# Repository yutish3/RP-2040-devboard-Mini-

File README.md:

### ABOUT 
rp-2040 dev board in small form factor of 3cm x 6cm made in kicad

it has :- 2 x 20 pin connectors , separate headers for HC - 05 Bluetooth module , extra 4Mb flash memory , USB c port , 2 buttons for BOOT and Reset and TC2030 connector for programming without usb c

# IMAGES

# SCHEMATICS 

# FOOTPRINTS

# PCB

# RENDER

Initially i tried to make it black but it changed color to smth random and it looks way cooler now 

# FILES
/Production folder has all the production files

/PCB files has all the pcb project files in it

# CREDITS

Kicad

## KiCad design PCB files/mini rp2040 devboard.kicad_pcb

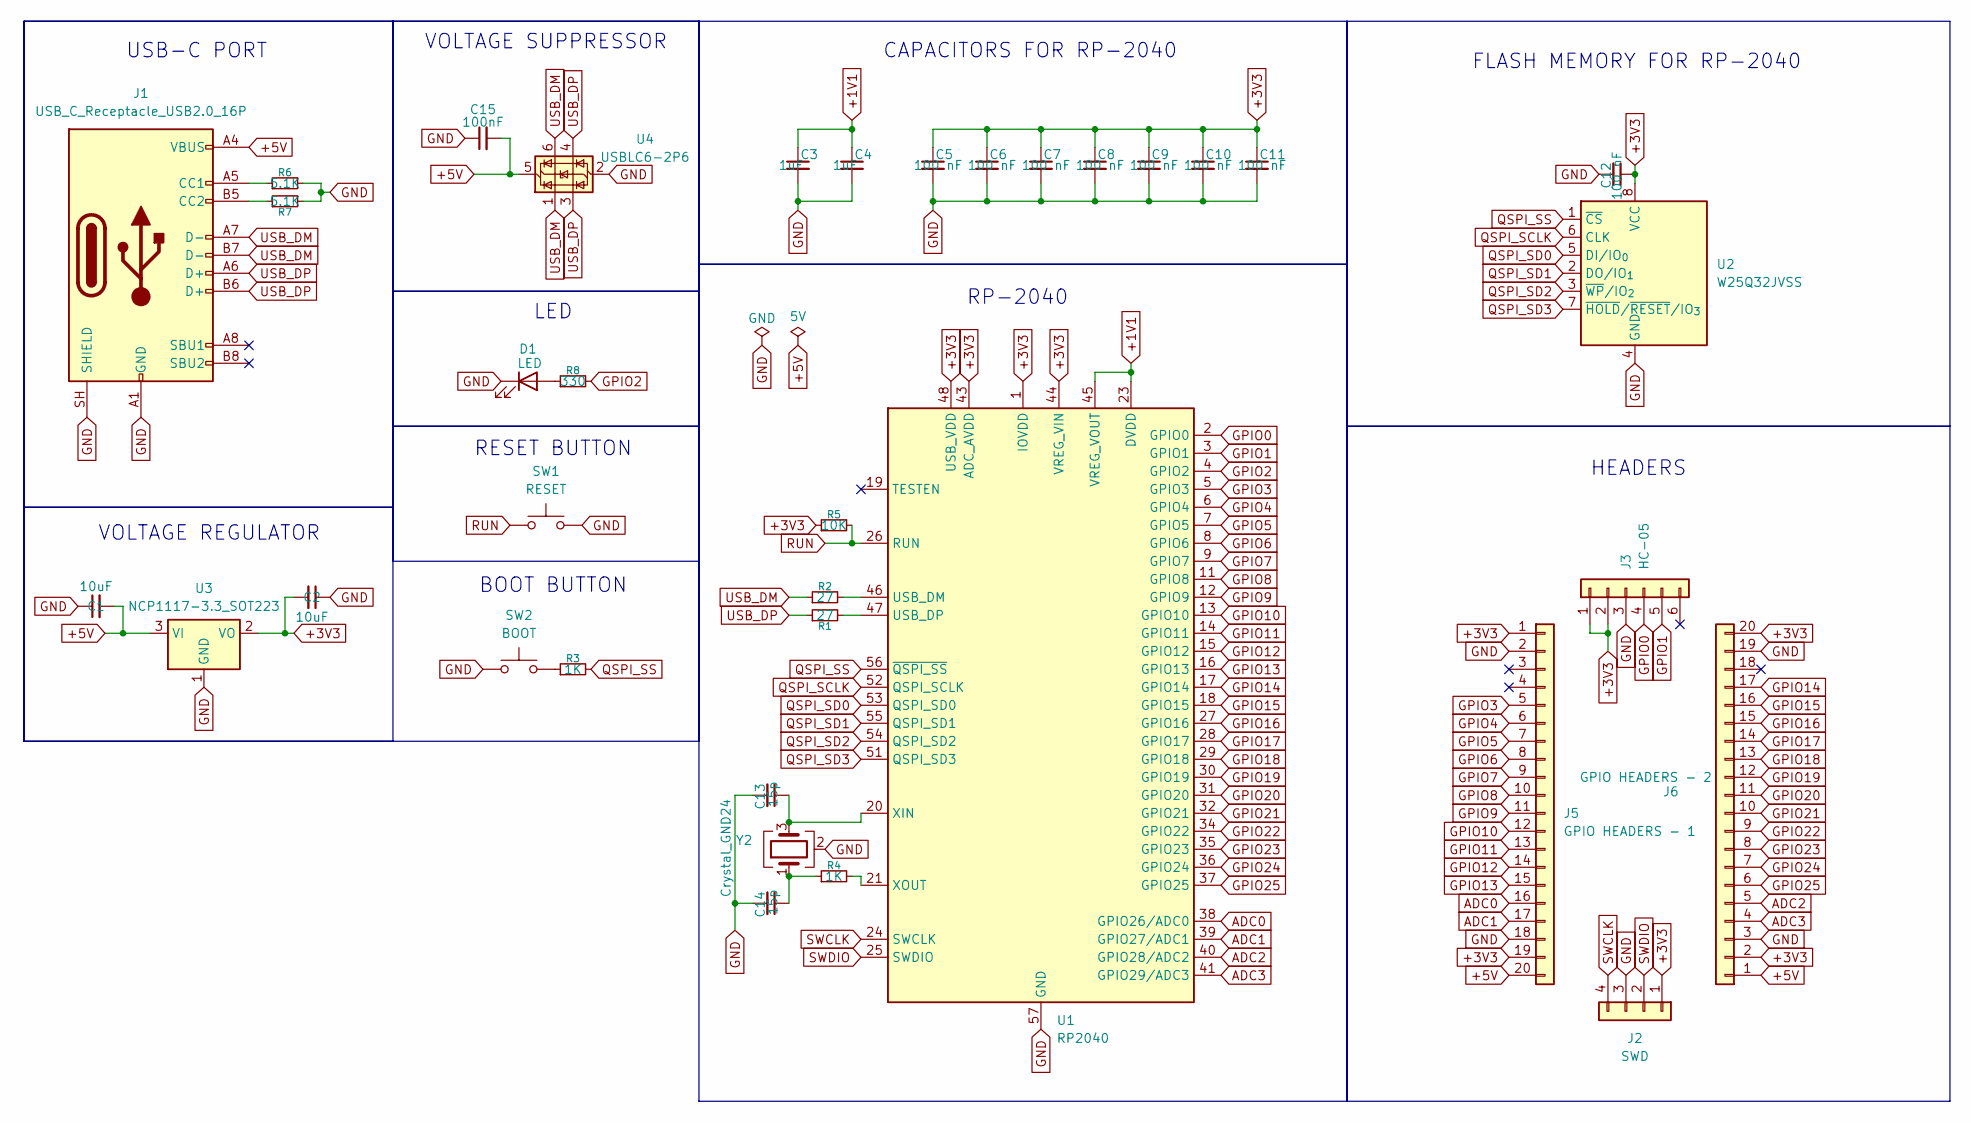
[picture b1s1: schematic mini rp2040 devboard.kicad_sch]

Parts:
C1, C2: 10uF; C_0201_0603Metric
C3, C4: 1uF; C_0201_0603Metric
C5, C6, C7, C8, C9, C10, C11, C12: 100 nF; C_0201_0603Metric
C13, C14: 15p; C_0201_0603Metric
C15: 100nF; C_0201_0603Metric
D1: LED; LED_0402_1005Metric
J1: USB_C_Receptacle_USB2.0_16P; USB_C_Receptacle_HCTL_HC-TYPE-C-16P-01A
J2: SWD; Tag-Connect_TC2030-IDC-NL_2x03_P1.27mm_Vertical
J3: HC-05; PinHeader_1x06_P2.54mm_Vertical
J5: GPIO HEADERS - 1; PinHeader_1x20_P2.54mm_Vertical
J6: GPIO HEADERS - 2; PinHeader_1x20_P2.54mm_Vertical
R1, R2: 27; R_0201_0603Metric
R3, R4: 1K; R_0201_0603Metric
R5: 10K; R_0201_0603Metric
R6, R7: 5.1K; R_0201_0603Metric
R8: 330; R_0201_0603Metric
SW1: RESET; SW_SPST_TS-1088-xR020
SW2: BOOT; SW_SPST_TS-1088-xR020
U1: RP2040; QFN-56-1EP_7x7mm_P0.4mm_EP3.2x3.2mm
U2: W25Q32JVSS; SOIC-8_5.3x5.3mm_P1.27mm
U3: NCP1117-3.3_SOT223; SOT-223-3_TabPin2
U4: USBLC6-2P6; SOT-666
Y2: Crystal_GND24; Crystal_SMD_2520-4Pin_2.5x2.0mm

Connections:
+1V1: C3.1, C4.1, U1.23 (DVDD), U1.45 (VREG_VOUT), U1.50 (DVDD)
+3V3: C2.2, C5.1, C6.1, C7.1, C8.1, C9.1, C10.1, C11.1, C12.1, J2.1, J3.1, J3.2, J5.1, J5.19, J6.2, J6.20, R5.1, U1.1 (IOVDD), U1.10 (IOVDD), U1.22 (IOVDD), U1.33 (IOVDD), U1.42 (IOVDD), U1.43 (ADC_AVDD), U1.44 (VREG_VIN), U1.48 (USB_VDD), U1.49 (IOVDD), U2.8 (VCC), U3.2 (VO)
+5V: C1.2, C15.2, J1.A4 (VBUS), J1.A9 (VBUS), J1.B4 (VBUS), J1.B9 (VBUS), J5.20, J6.1, U3.3 (VI), U4.5 (VBUS)
ADC0: J5.16, U1.38 (GPIO26/ADC0)
ADC1: J5.17, U1.39 (GPIO27/ADC1)
ADC2: J6.5, U1.40 (GPIO28/ADC2)
ADC3: J6.4, U1.41 (GPIO29/ADC3)
GND: C1.1, C2.1, C3.2, C4.2, C5.2, C6.2, C7.2, C8.2, C9.2, C10.2, C11.2, C12.2, C13.2, C14.2, C15.1, D1.1 (K), J1.A1 (GND), J1.A12 (GND), J1.B1 (GND), J1.B12 (GND), J1.SH (SHIELD), J2.3, J3.3, J5.2, J5.18, J6.3, J6.19, R6.2, R7.2, SW1.2, SW2.1, U1.57 (GND), U2.4 (GND), U3.1 (GND), U4.2 (GND), Y2.2 (G), Y2.4 (G)
GPIO0: J3.4, U1.2 (GPIO0)
GPIO1: J3.5, U1.3 (GPIO1)
GPIO2: R8.2, U1.4 (GPIO2)
GPIO3: J5.5, U1.5 (GPIO3)
GPIO4: J5.6, U1.6 (GPIO4)
GPIO5: J5.7, U1.7 (GPIO5)
GPIO6: J5.8, U1.8 (GPIO6)
GPIO7: J5.9, U1.9 (GPIO7)
GPIO8: J5.10, U1.11 (GPIO8)
GPIO9: J5.11, U1.12 (GPIO9)
GPIO10: J5.12, U1.13 (GPIO10)
GPIO11: J5.13, U1.14 (GPIO11)
GPIO12: J5.14, U1.15 (GPIO12)
GPIO13: J5.15, U1.16 (GPIO13)
GPIO14: J6.17, U1.17 (GPIO14)
GPIO15: J6.16, U1.18 (GPIO15)
GPIO16: J6.15, U1.27 (GPIO16)
GPIO17: J6.14, U1.28 (GPIO17)
GPIO18: J6.13, U1.29 (GPIO18)
GPIO19: J6.12, U1.30 (GPIO19)
GPIO20: J6.11, U1.31 (GPIO20)
GPIO21: J6.10, U1.32 (GPIO21)
GPIO22: J6.9, U1.34 (GPIO22)
GPIO23: J6.8, U1.35 (GPIO23)
GPIO24: J6.7, U1.36 (GPIO24)
GPIO25: J6.6, U1.37 (GPIO25)
unnamed: C14.1, R4.1, Y2.1
unnamed: D1.2 (A), R8.1
unnamed: J1.A5 (CC1), R6.1
unnamed: J1.B5 (CC2), R7.1
unnamed: R3.1, SW2.2
unnamed: R2.2, U1.46 (USB_DM)
unnamed: R1.2, U1.47 (USB_DP)
unnamed: C13.1, U1.20 (XIN), Y2.3
unnamed: R4.2, U1.21 (XOUT)
QSPI_SCLK: U1.52 (QSPI_SCLK), U2.6 (CLK)
QSPI_SD0: U1.53 (QSPI_SD0), U2.5 (DI/IO_{0})
QSPI_SD1: U1.55 (QSPI_SD1), U2.2 (DO/IO_{1})
QSPI_SD2: U1.54 (QSPI_SD2), U2.3 (~WP/IO_{2})
QSPI_SD3: U1.51 (QSPI_SD3), U2.7 (~HOLD/~RESET/IO_{3})
QSPI_SS: R3.2, U1.56 (~QSPI_SS), U2.1 (~CS)
RUN: R5.2, SW1.1, U1.26 (RUN)
SWCLK: J2.4, U1.24 (SWCLK)
SWDIO: J2.2, U1.25 (SWDIO)
USB_DM: J1.A7 (D-), J1.B7 (D-), R2.1, U4.1 (I/O1), U4.6 (I/O1)
USB_DP: J1.A6 (D+), J1.B6 (D+), R1.1, U4.3 (I/O2), U4.4 (I/O2)

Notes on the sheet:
FLASH MEMORY FOR RP-2040
RP-2040
BOOT BUTTON
USB-C PORT
RESET BUTTON
CAPACITORS FOR RP-2040
VOLTAGE REGULATOR
VOLTAGE SUPPRESSOR
LED
HEADERS

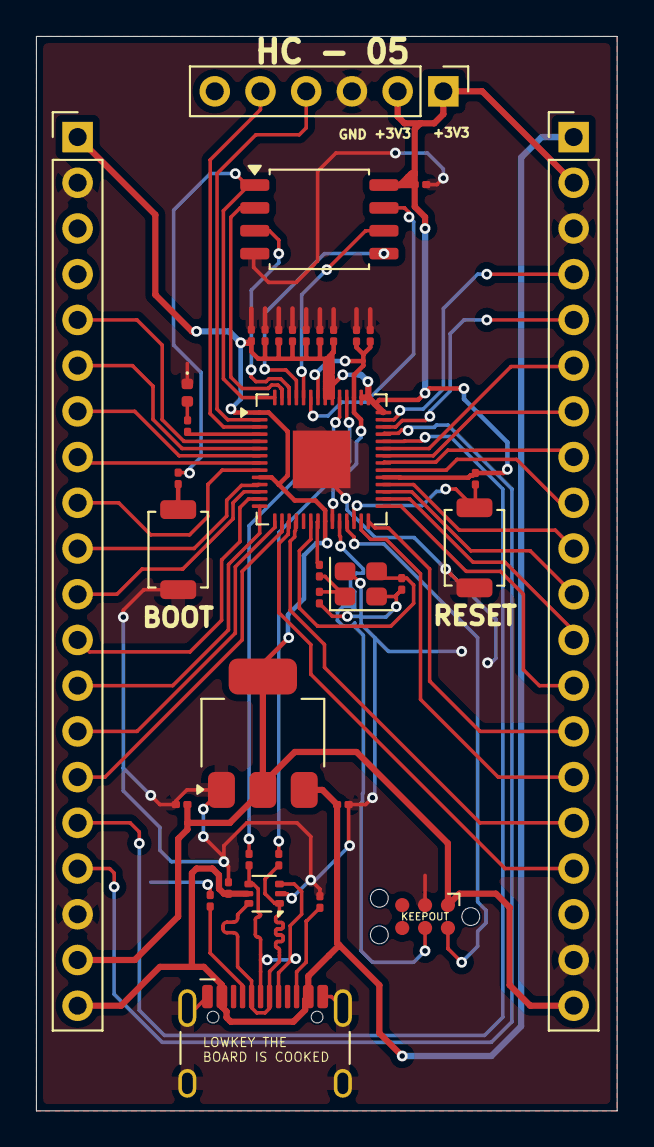
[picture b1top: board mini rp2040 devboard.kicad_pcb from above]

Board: 2 copper layers, 32.3 x 59.7 mm, 36 parts (0 on the bottom side), 54 nets.

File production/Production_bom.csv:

Designator,Footprint,Quantity,Value,LCSC Part #
"C1, C2",0201,2,10uF,
"C10, C11, C12, C5, C6, C7, C8, C9",0201,8,100 nF,
"C13, C14",0201,2,15p,
C15,0201,1,100nF,
"C3, C4",0201,2,1uF,
D1,0402,1,LED,
J1,USB_C_Receptacle_HCTL_HC-TYPE-C-16P-01A,1,USB_C_Receptacle_USB2.0_16P,
J2,Tag-Connect_TC2030-IDC-NL_2x03_P1.27mm_Vertical,1,SWD,
J3,PinHeader_1x06_P2.54mm_Vertical,1,HC-05,
J5,PinHeader_1x20_P2.54mm_Vertical,1,GPIO HEADERS - 1,
J6,PinHeader_1x20_P2.54mm_Vertical,1,GPIO HEADERS - 2,
"R1, R2",0201,2,27,
"R3, R4",0201,2,1K,
R5,0201,1,10K,
"R6, R7",0201,2,5.1K,
R8,0201,1,330,
SW1,SW_SPST_TS-1088-xR020,1,RESET,
SW2,SW_SPST_TS-1088-xR020,1,BOOT,
U1,QFN-56-1EP_7x7mm_P0.4mm_EP3.2x3.2mm,1,RP2040,
U2,SOIC-8_5.3x5.3mm_P1.27mm,1,W25Q32JVSS,
U3,SOT-223-3_TabPin2,1,NCP1117-3.3_SOT223,
U4,SOT-666,1,USBLC6-2P6,
Y2,Crystal_SMD_2520-4Pin_2.5x2.0mm,1,Crystal_GND24,
